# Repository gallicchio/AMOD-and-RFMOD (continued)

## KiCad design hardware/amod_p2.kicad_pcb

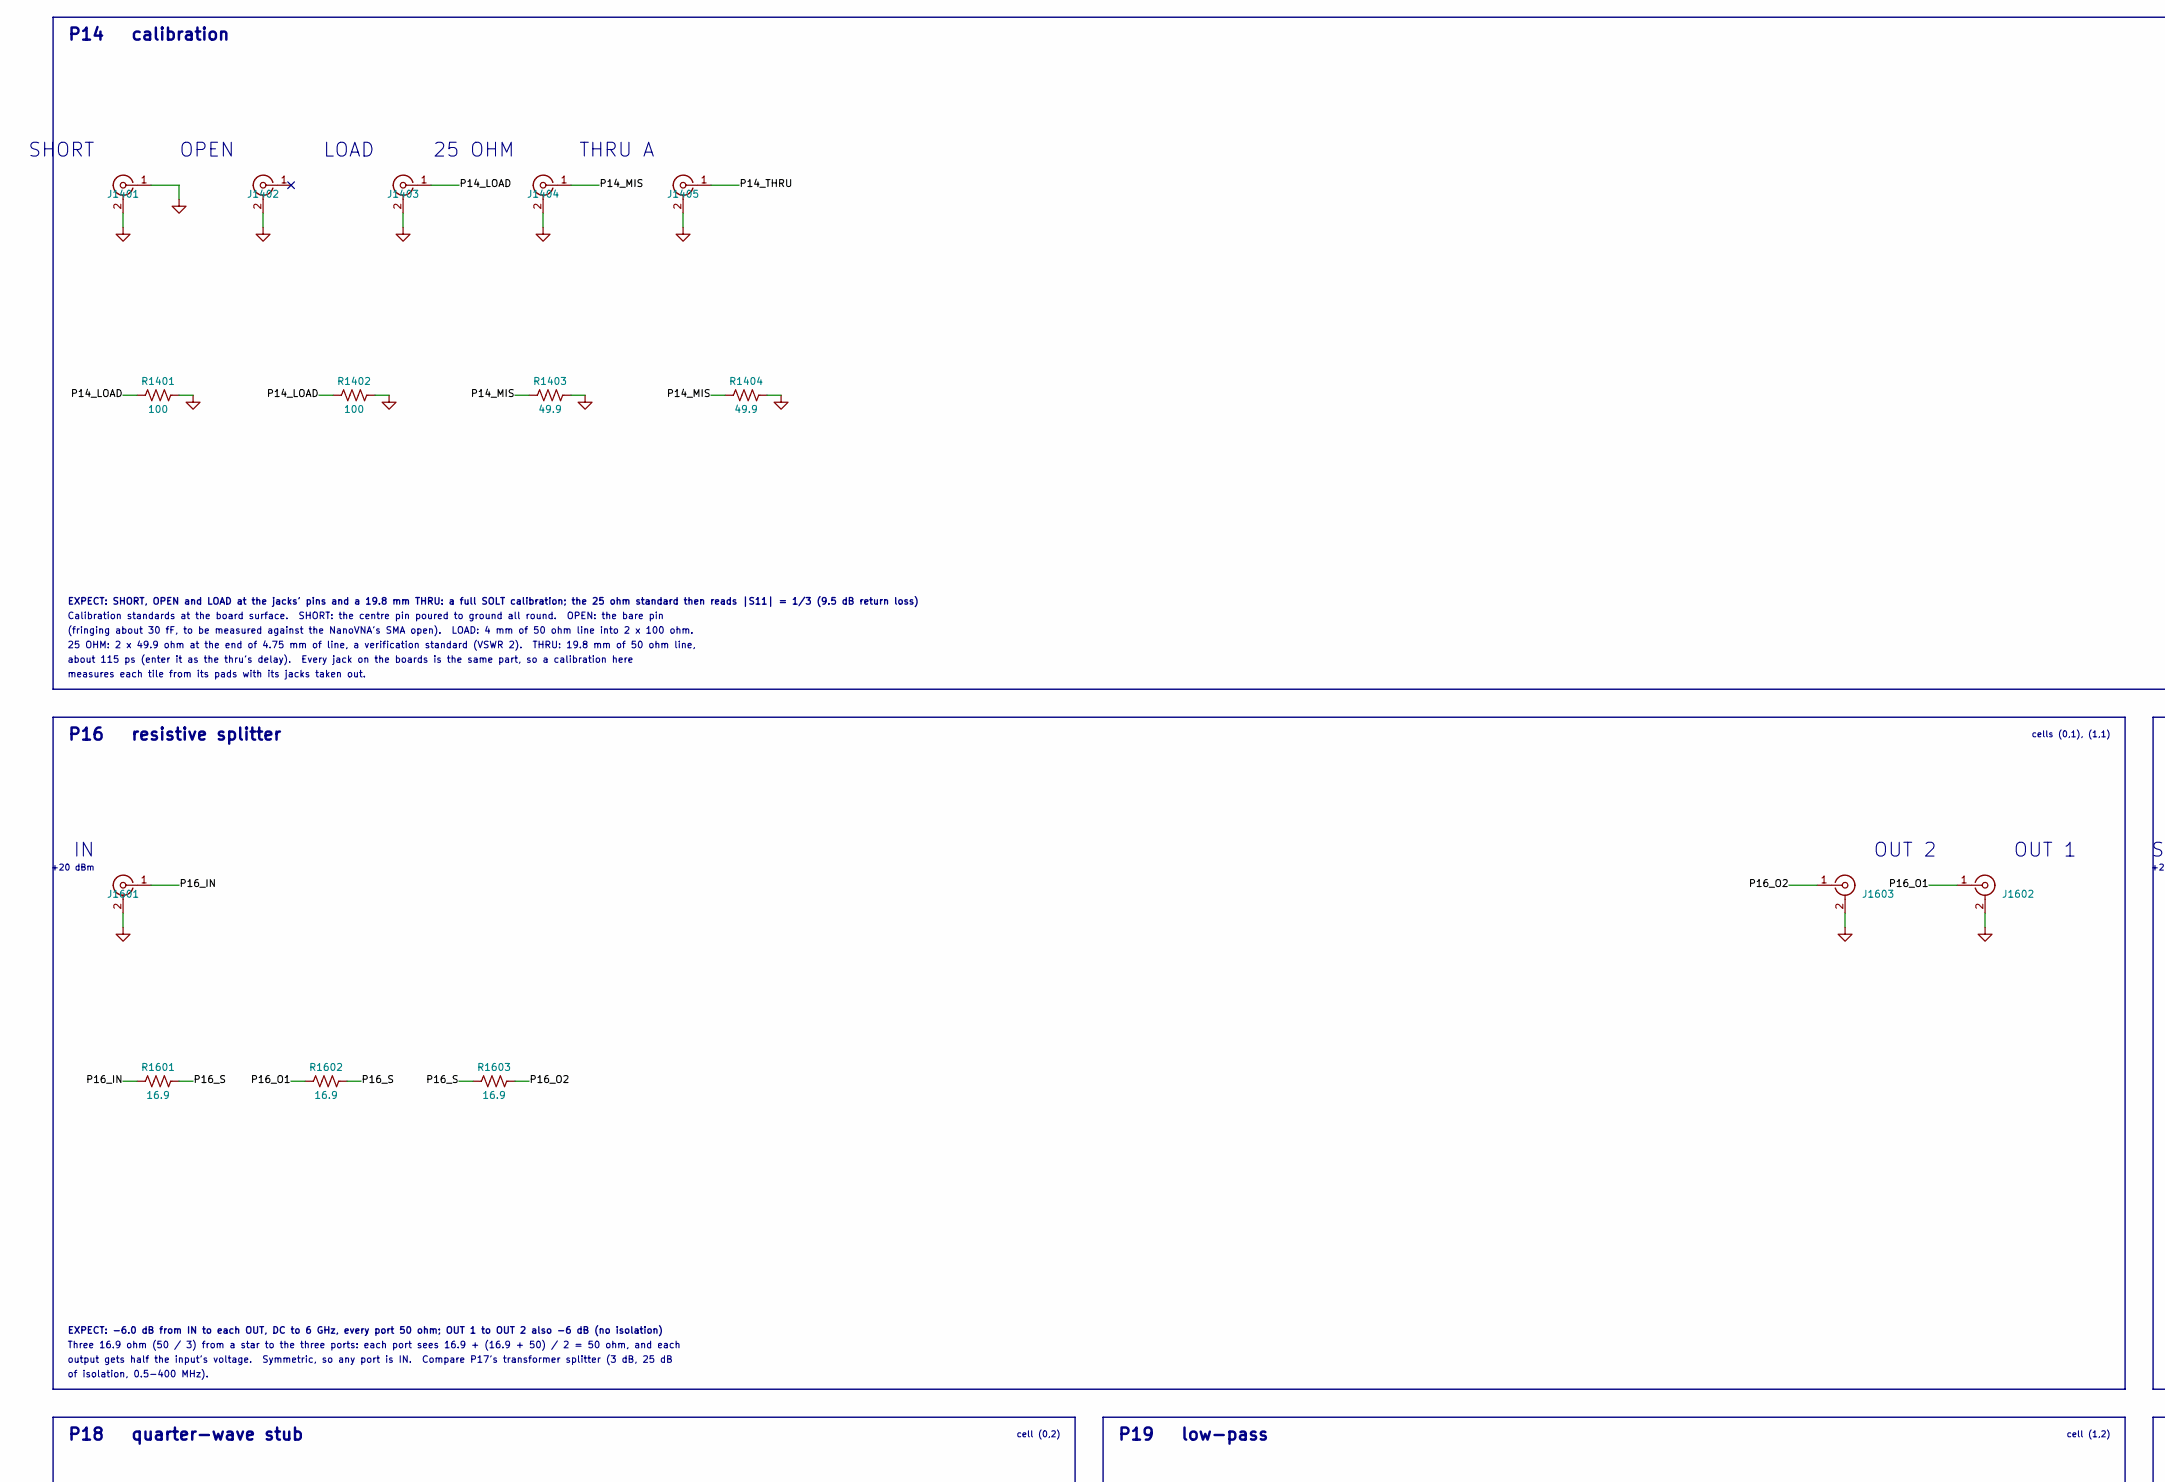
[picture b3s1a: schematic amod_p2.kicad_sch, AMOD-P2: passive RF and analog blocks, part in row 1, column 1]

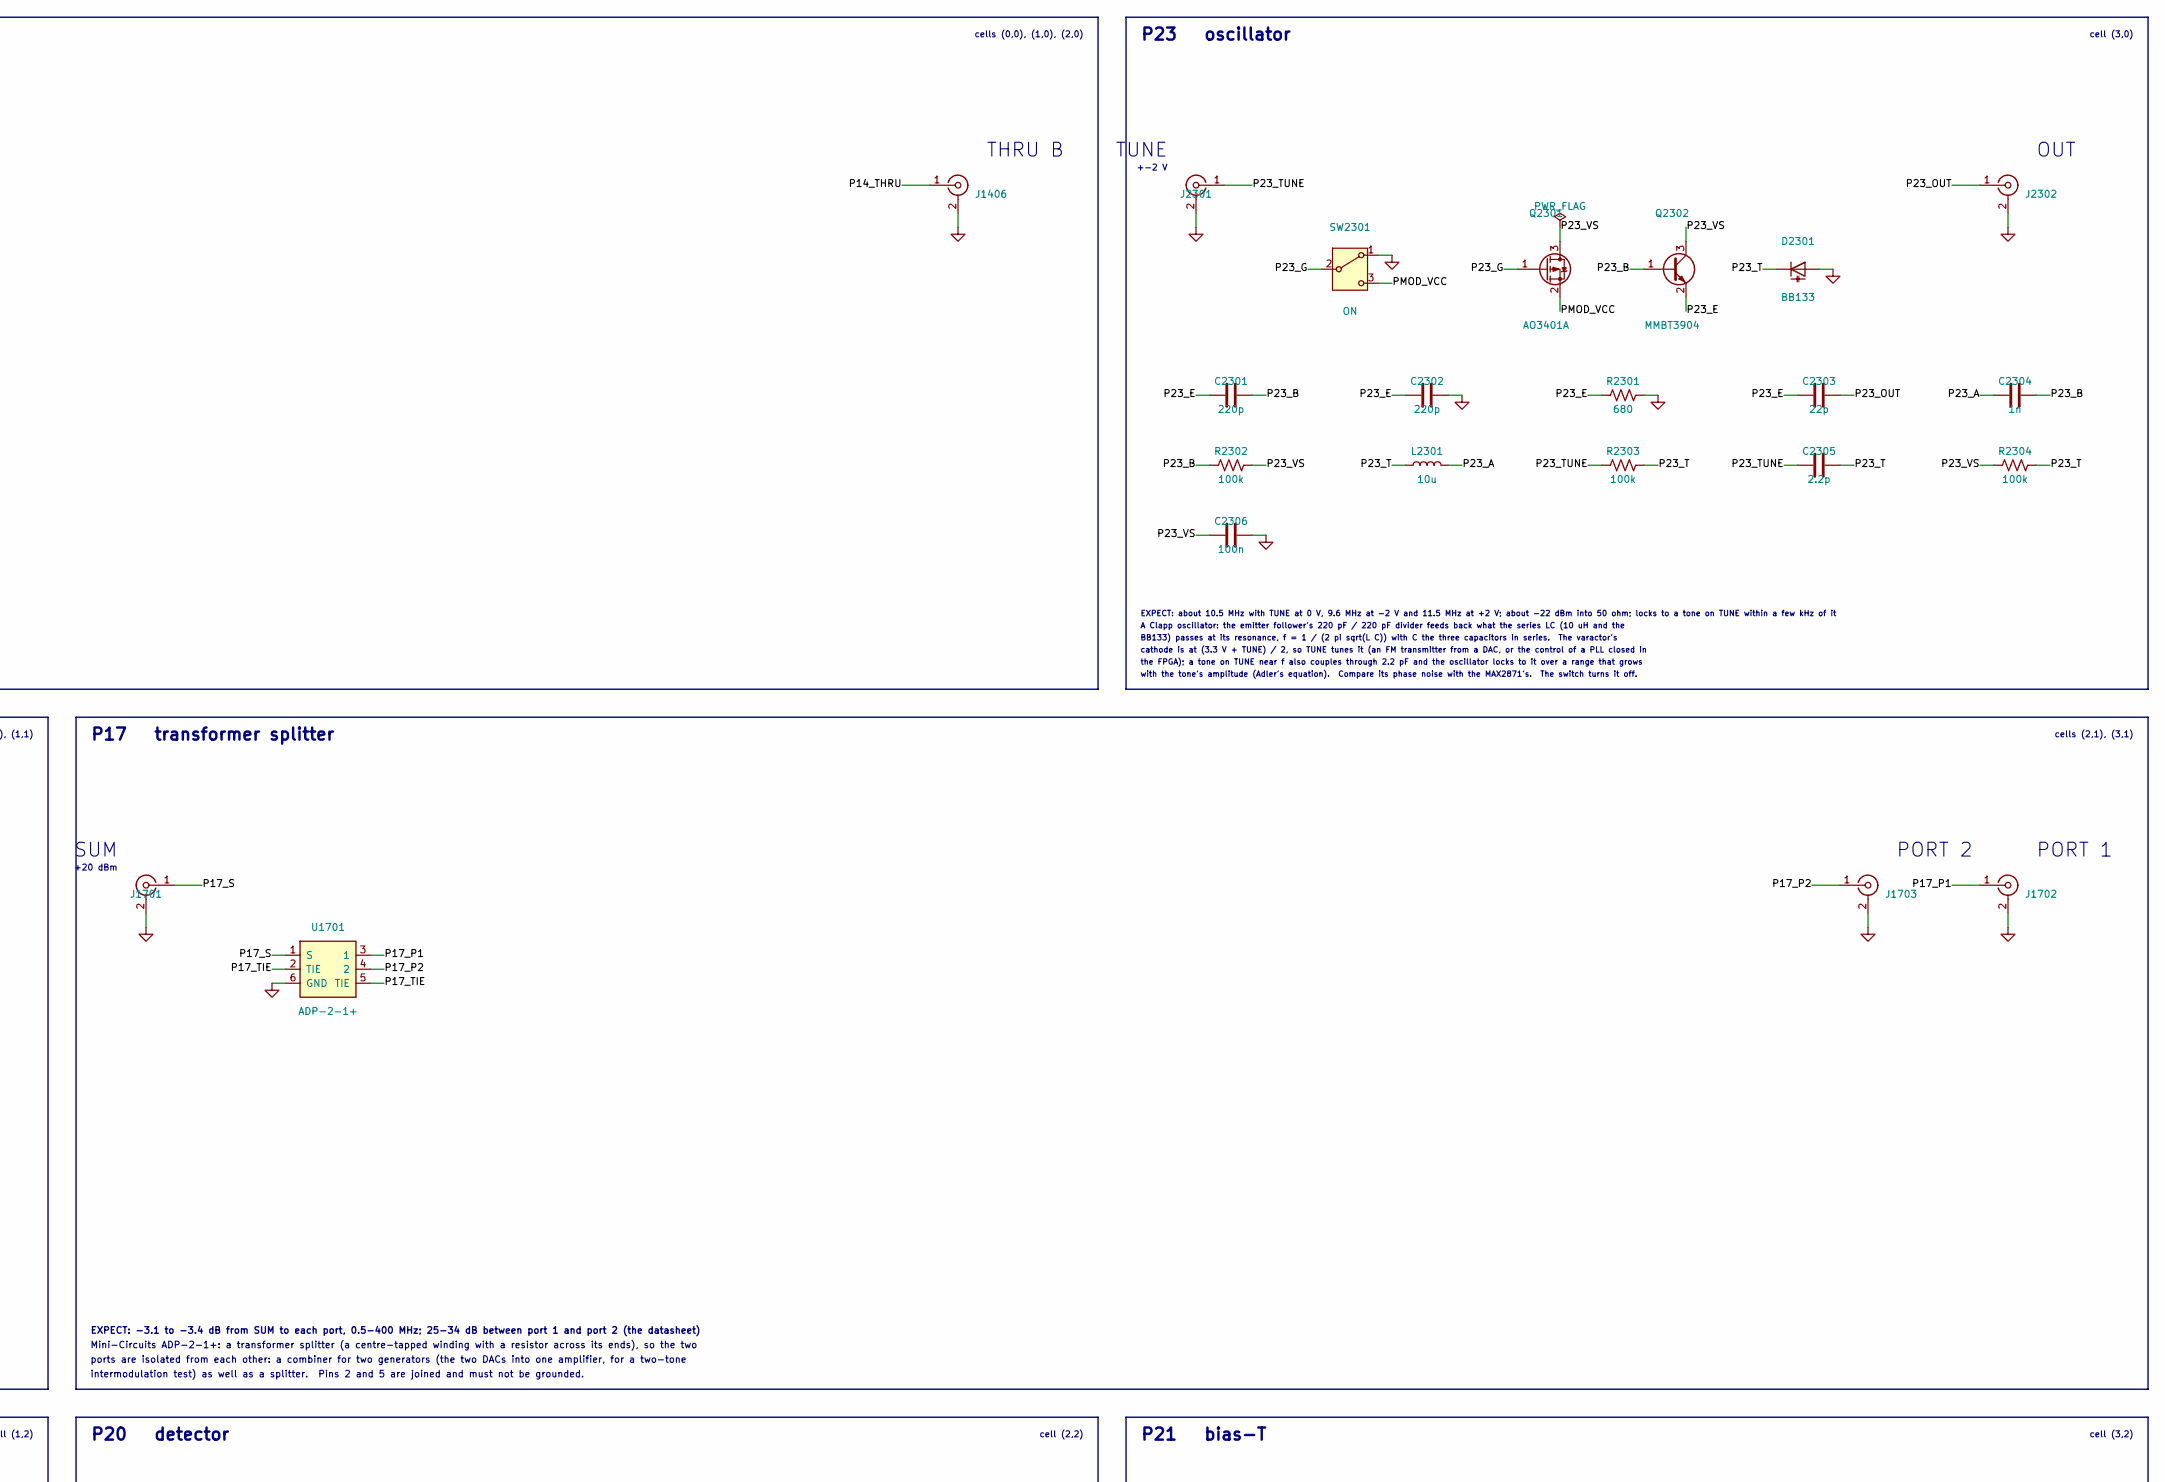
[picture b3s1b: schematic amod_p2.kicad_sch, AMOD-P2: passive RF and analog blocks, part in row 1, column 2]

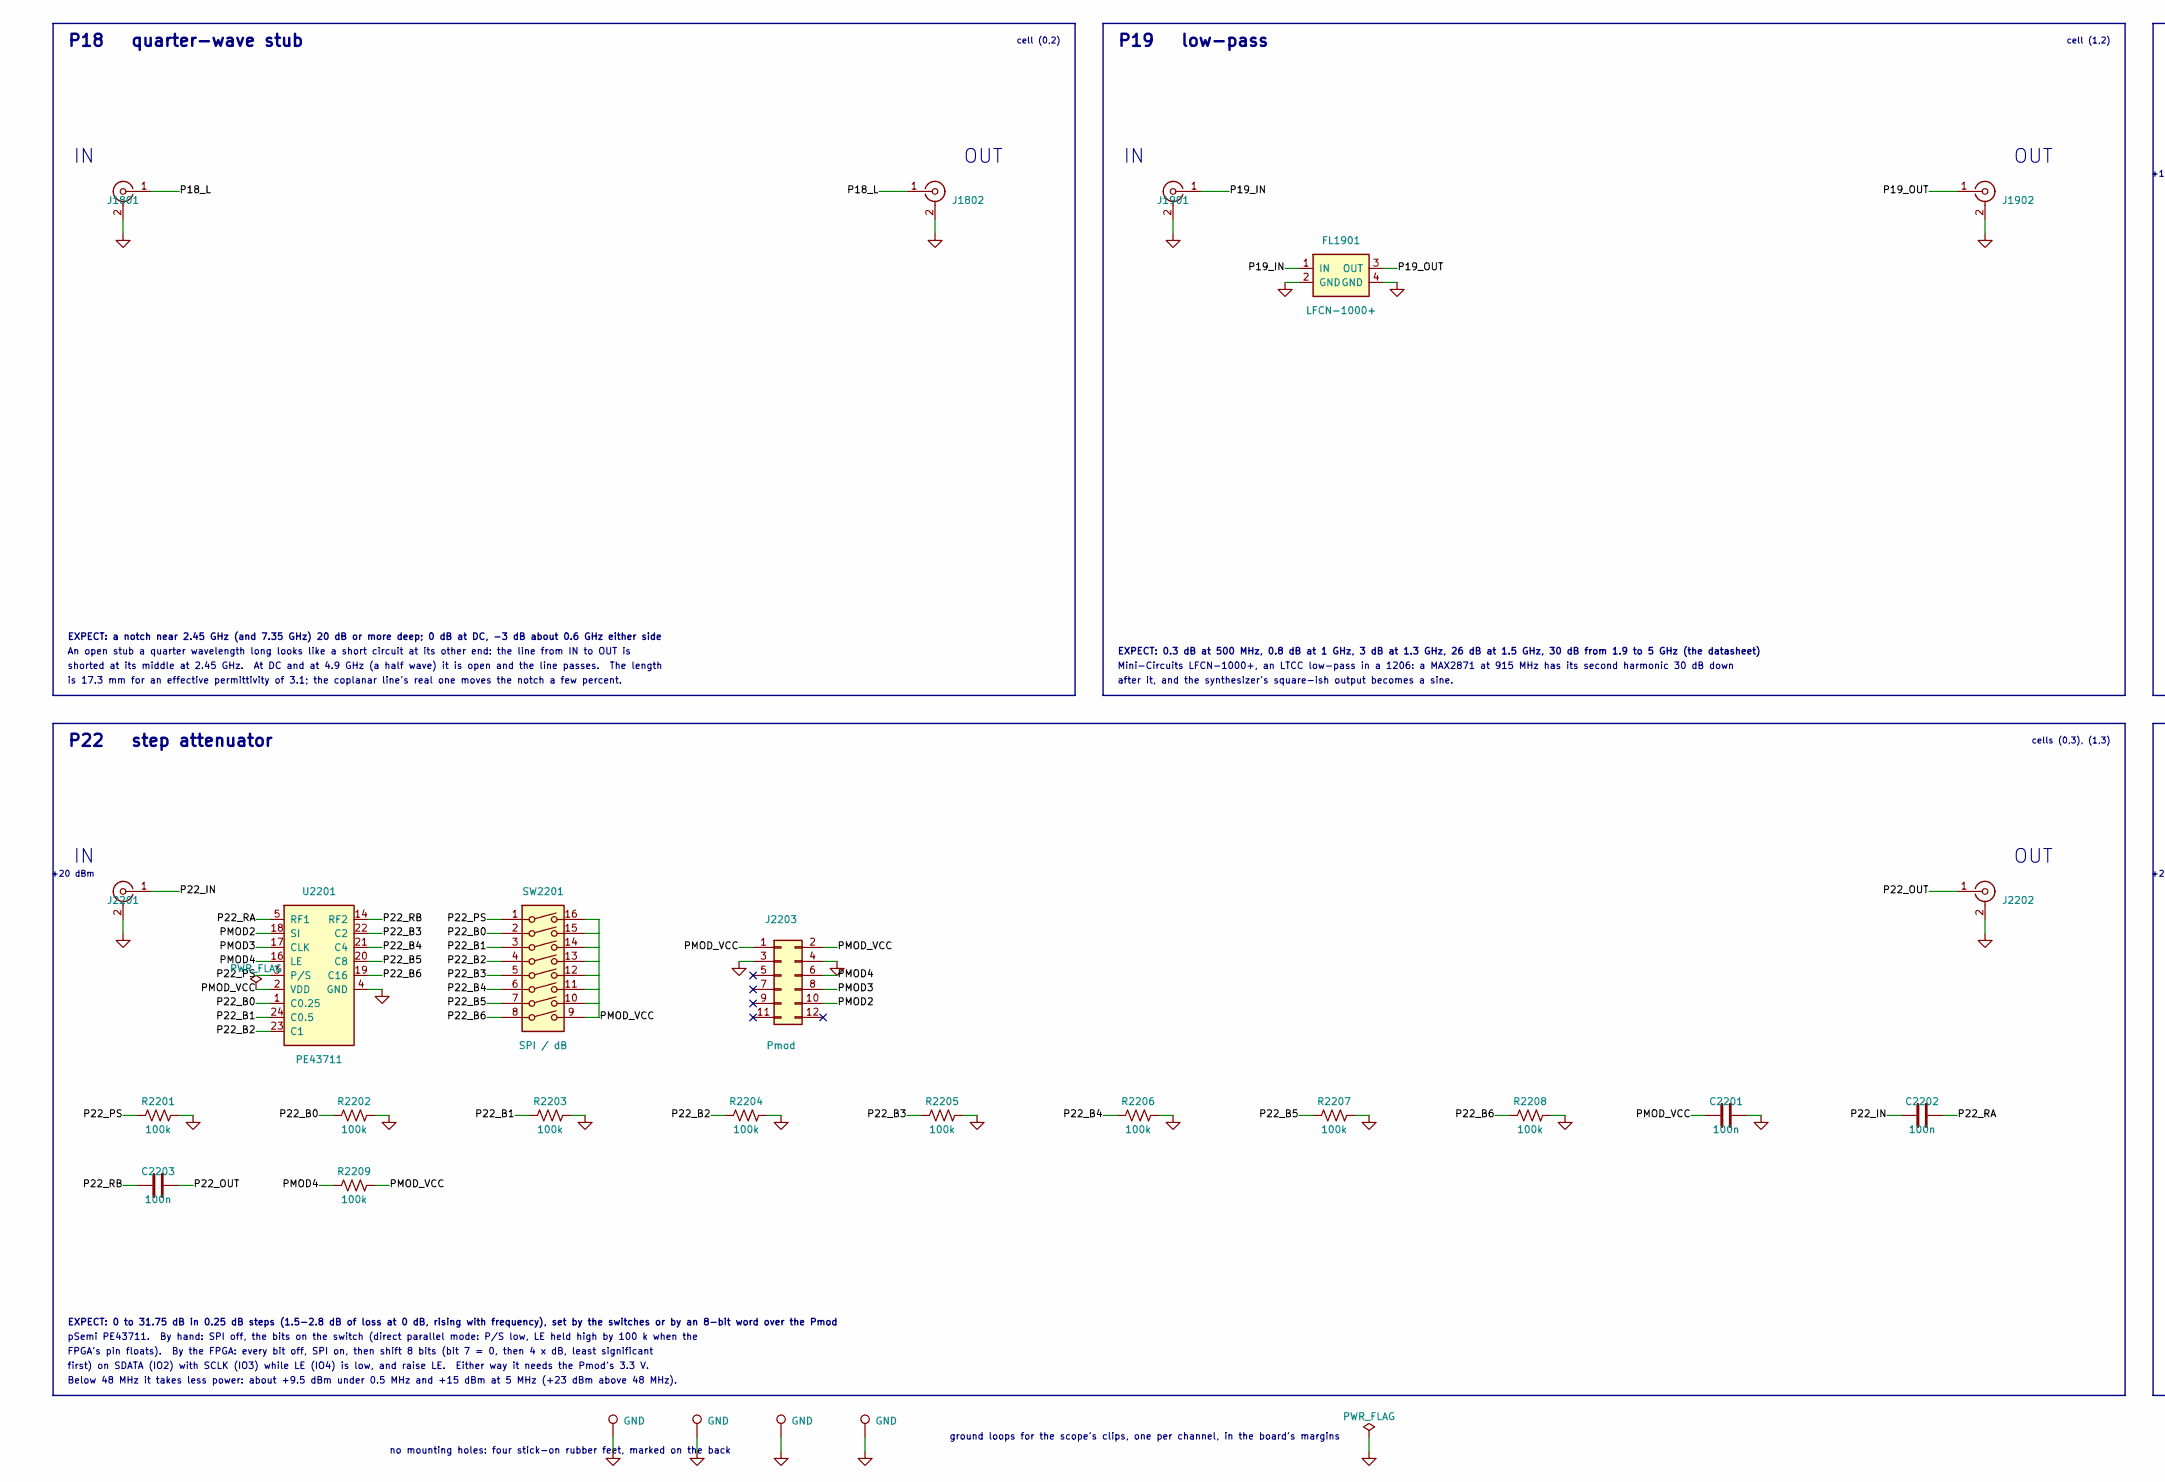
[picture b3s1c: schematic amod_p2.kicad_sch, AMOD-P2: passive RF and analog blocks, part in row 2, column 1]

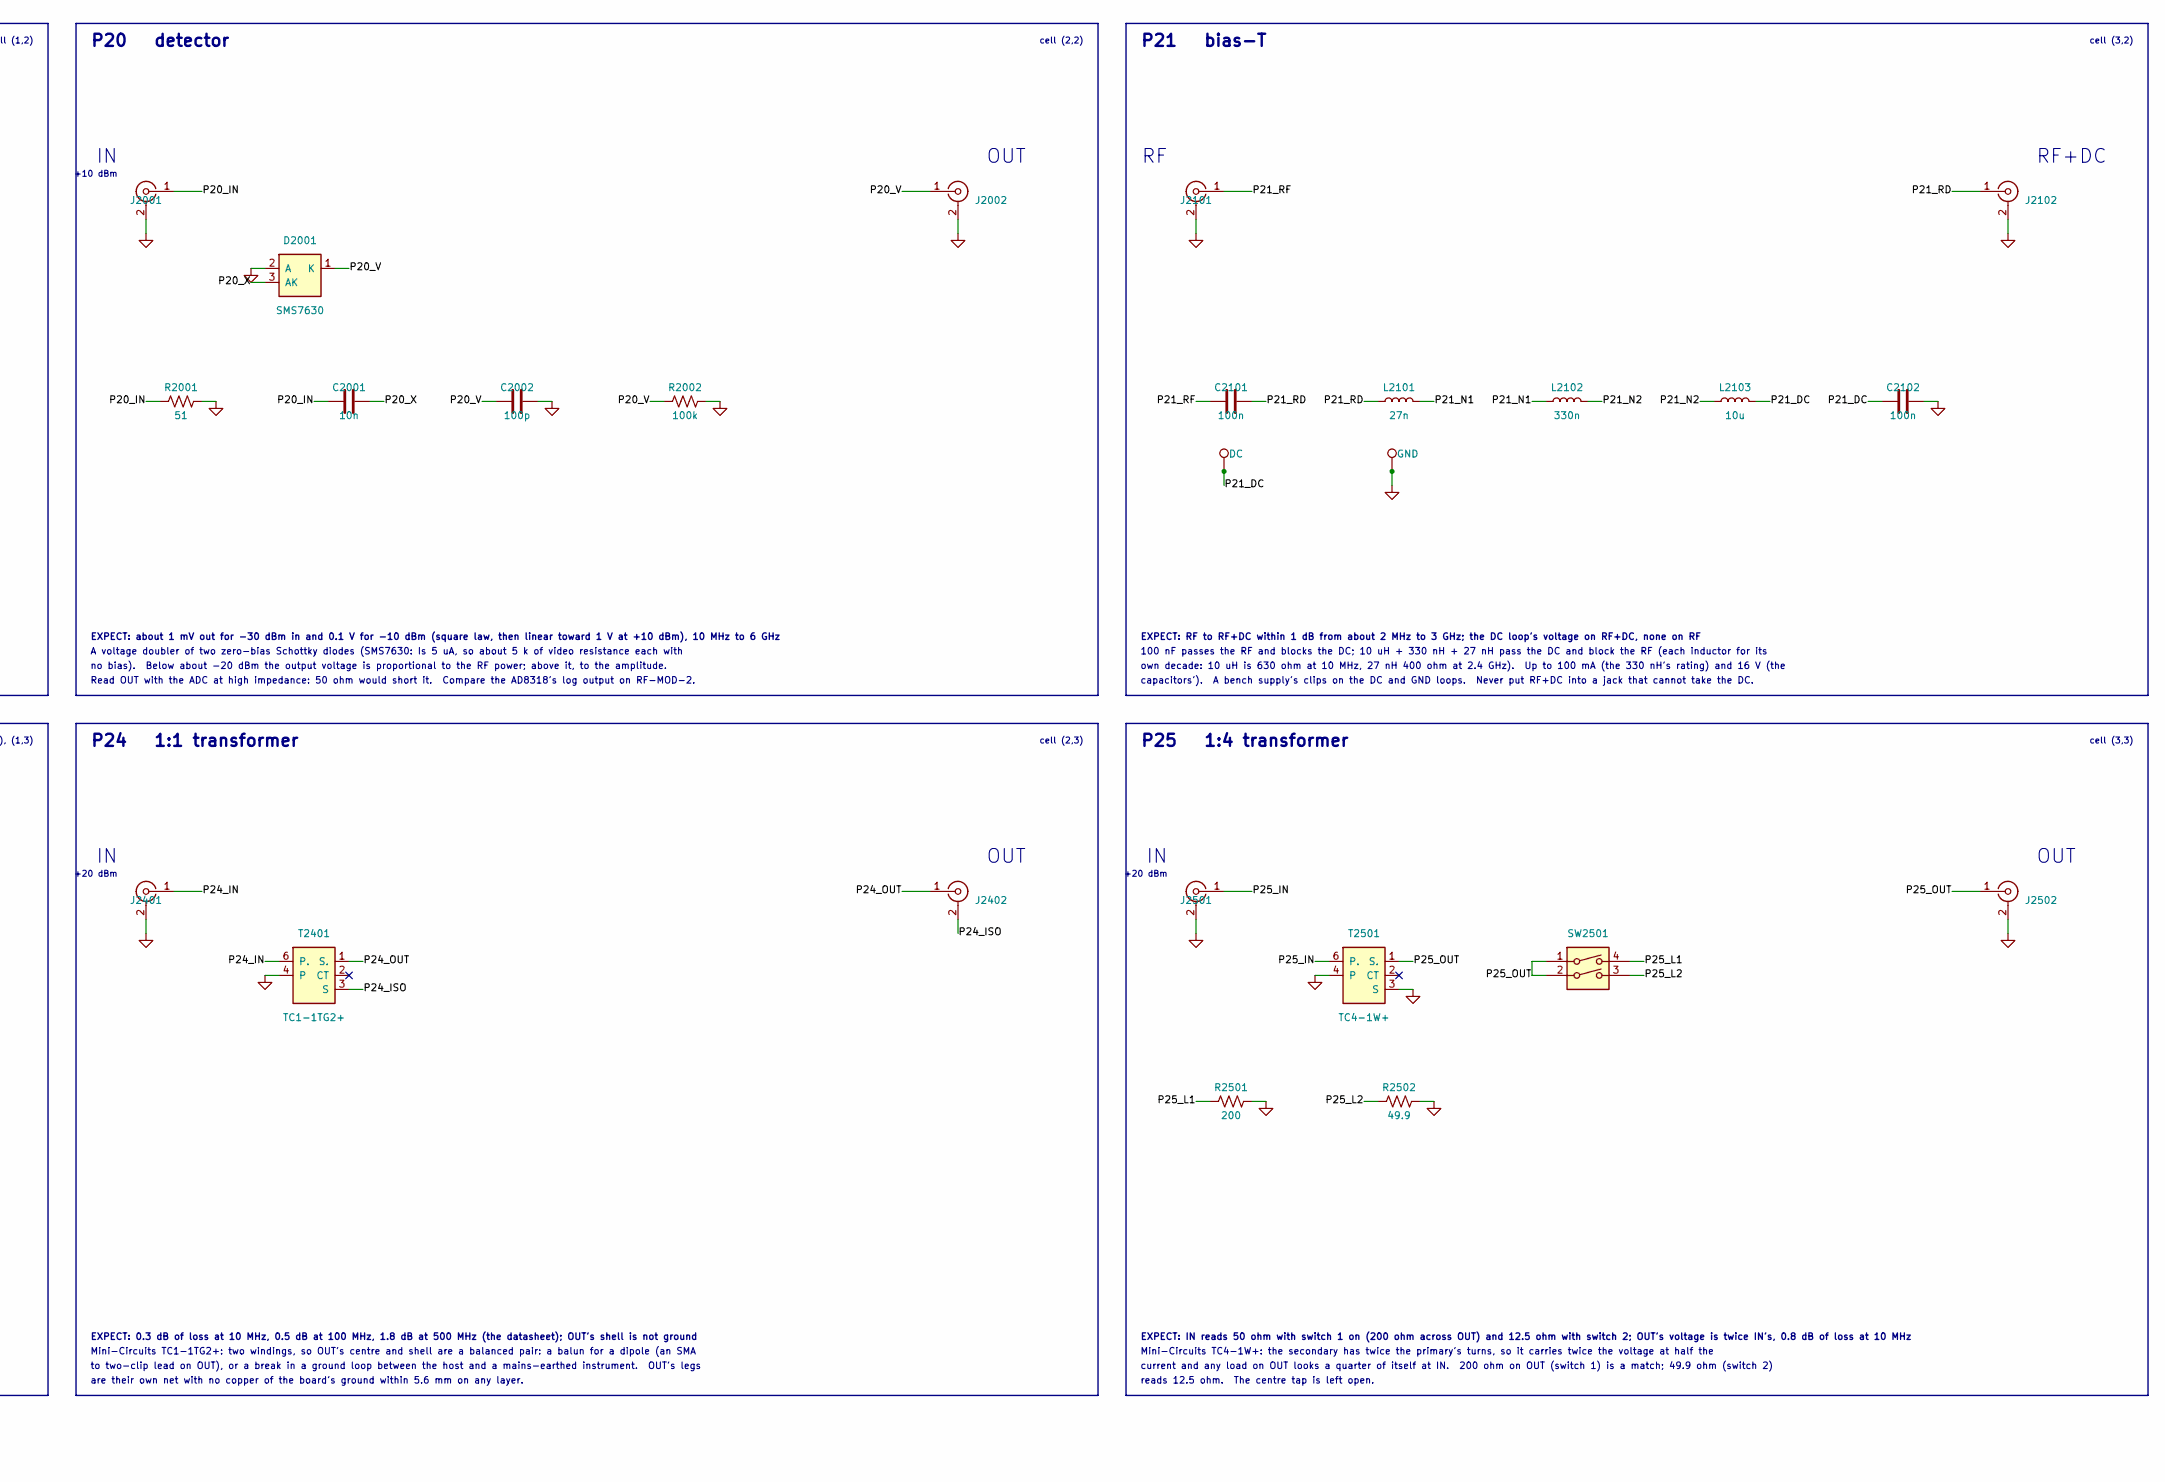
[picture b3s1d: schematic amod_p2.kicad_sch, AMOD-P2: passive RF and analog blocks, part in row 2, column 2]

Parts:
C2001: 10n; C_0402_1005Metric; MPN CL05B103KB5NNNC; LCSC C15195
C2002: 100p; C_0402_1005Metric; MPN 0402CG101J500NT; LCSC C1546
C2101, C2102, C2201, C2202, C2203, C2306: 100n; C_0402_1005Metric; MPN CL05B104KO5NNNC; LCSC C1525
C2301, C2302: 220p; C_0402_1005Metric; MPN 0402CG221J500NT; LCSC C39122
C2303: 22p; C_0402_1005Metric; MPN 0402CG220J500NT; LCSC C1555
C2304: 1n; C_0402_1005Metric; MPN 0402B102K500NT; LCSC C1523
C2305: 2.2p; C_0402_1005Metric; MPN 0402CG2R2C500NT; LCSC C1559
D2001: SMS7630; SOT-23; MPN SMS7630-006LF; LCSC C6489012
D2301: BB133; D_SOD-323; MPN BB133; LCSC C5334579
FL1901: LFCN-1000+; Filter_LTCC_1206_LFCN; MPN LFCN-1000+; LCSC C879868
J1401, J1402, J1403, J1404, J1405, J1406, J1601, J1602, J1603, J1701, J1702, J1703, J1801, J1802, J1901, J1902, J2001, J2002, J2101, J2102, J2201, J2202, J2301, J2302, J2401, J2402, J2501, J2502: SMA; SMA_BWSMA-KE-Z001_Vertical; MPN BWSMA-KE-Z001; LCSC C496549
J2203: Pmod; PinHeader_2x06_P2.54mm_Horizontal_PZ254R-12-12P; MPN PZ254R-12-12P; LCSC C492434
L2101: 27n; L_0402_1005Metric; MPN LQW15AN27NG80D; LCSC C882469
L2102: 330n; L_0603_1608Metric; MPN CS0603-R33J-S; LCSC C142165
L2103, L2301: 10u; L_1210_3225Metric; MPN NLV32T-100J-PF; LCSC C76835
Q2301: AO3401A; SOT-23; MPN AO3401A; LCSC C15127
Q2302: MMBT3904; SOT-23; MPN MMBT3904(RANGE:100-300); LCSC C20526
R1401, R1402: 100; R_0402_1005Metric; MPN 0402WGF1000TCE; LCSC C25076
R1403, R1404, R2502: 49.9; R_0402_1005Metric; MPN 0402WGF499JTCE; LCSC C25120
R1601, R1602, R1603: 16.9; R_0402_1005Metric; MPN 0402WGF169JTCE; LCSC C82287
R2001: 51; R_0402_1005Metric; MPN 0402WGF510JTCE; LCSC C25125
R2002, R2201, R2202, R2203, R2204, R2205, R2206, R2207, R2208, R2209, R2302, R2303, R2304: 100k; R_0402_1005Metric; MPN 0402WGF1003TCE; LCSC C25741
R2301: 680; R_0402_1005Metric; MPN 0402WGF6800TCE; LCSC C25130
R2501: 200; R_0402_1005Metric; MPN 0402WGF2000TCE; LCSC C25087
SW2201: SPI / dB; SW_DIP_SPSTx08_Slide_1.27mm_DSHP08; MPN DSHP08TSGET; LCSC C40738
SW2301: ON; SW_SPDT_Shouhan_MSK12C02; MPN MSK12C02; LCSC C431540
SW2501: LOAD; SW_DIP_SPSTx02_Slide_1.27mm_DSHP02; MPN DSHP02TSGET; LCSC C40735
T2401: TC1-1TG2+; MiniCircuits_AT224_5P; MPN TC1-1TG2+; LCSC C3305009
T2501: TC4-1W+; MiniCircuits_AT224_5P; MPN TC4-1W+; LCSC C879855
TP2101: DC; TestPoint_Loop_RH-5019; MPN RH-5019; LCSC C5199800
TP2102, TP9901, TP9902, TP9903, TP9904: GND; TestPoint_Loop_RH-5019; MPN RH-5019; LCSC C5199800
U1701: ADP-2-1+; MiniCircuits_CD636_ADP-2-1; MPN ADP-2-1+; LCSC C2683460
U2201: PE43711; QFN-24-1EP_4x4mm_P0.5mm_EP2.7x2.7mm; MPN PE43711B-Z; LCSC C470929

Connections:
/P14_LOAD: J1403.1 (In), R1401.1, R1402.1
/P14_MIS: J1404.1 (In), R1403.1, R1404.1
/P14_THRU: J1405.1 (In), J1406.1 (In)
/P16_IN: J1601.1 (In), R1601.1
/P16_O1: J1602.1 (In), R1602.1
/P16_O2: J1603.1 (In), R1603.2
/P16_S: R1601.2, R1602.2, R1603.1
/P17_P1: J1702.1 (In), U1701.3 (1)
/P17_P2: J1703.1 (In), U1701.4 (2)
/P17_S: J1701.1 (In), U1701.1 (S)
/P17_TIE: U1701.2 (TIE), U1701.5 (TIE)
/P18_L: J1801.1 (In), J1802.1 (In)
/P19_IN: FL1901.1 (IN), J1901.1 (In)
/P19_OUT: FL1901.3 (OUT), J1902.1 (In)
/P20_IN: C2001.1, J2001.1 (In), R2001.1
/P20_V: C2002.1, D2001.1 (K), J2002.1 (In), R2002.1
/P20_X: C2001.2, D2001.3 (AK)
/P21_DC: C2102.1, L2103.2, TP2101.1
/P21_N1: L2101.2, L2102.1
/P21_N2: L2102.2, L2103.1
/P21_RD: C2101.2, J2102.1 (In), L2101.1
/P21_RF: C2101.1, J2101.1 (In)
/P22_B0: R2202.1, SW2201.2, U2201.1 (C0.25)
/P22_B1: R2203.1, SW2201.3, U2201.24 (C0.5)
/P22_B2: R2204.1, SW2201.4, U2201.23 (C1)
/P22_B3: R2205.1, SW2201.5, U2201.22 (C2)
/P22_B4: R2206.1, SW2201.6, U2201.21 (C4)
/P22_B5: R2207.1, SW2201.7, U2201.20 (C8)
/P22_B6: R2208.1, SW2201.8, U2201.19 (C16)
/P22_IN: C2202.1, J2201.1 (In)
/P22_OUT: C2203.2, J2202.1 (In)
/P22_PS: R2201.1, SW2201.1, U2201.3 (P/S)
/P22_RA: C2202.2, U2201.5 (RF1)
/P22_RB: C2203.1, U2201.14 (RF2)
/P23_A: C2304.1, L2301.2
/P23_B: C2301.2, C2304.2, Q2302.1 (B), R2302.1
/P23_E: C2301.1, C2302.1, C2303.1, Q2302.2 (E), R2301.1
/P23_G: Q2301.1 (G), SW2301.2 (B)
/P23_OUT: C2303.2, J2302.1 (In)
/P23_T: C2305.2, D2301.1 (K), L2301.1, R2303.2, R2304.2
/P23_TUNE: C2305.1, J2301.1 (In), R2303.1
/P23_VS: C2306.1, Q2301.3 (D), Q2302.3 (C), R2302.2, R2304.1
/P24_IN: J2401.1 (In), T2401.6 (P.)
/P24_ISO: J2402.2 (Ext), T2401.3 (S)
/P24_OUT: J2402.1 (In), T2401.1 (S.)
/P25_IN: J2501.1 (In), T2501.6 (P.)
/P25_L1: R2501.1, SW2501.4
/P25_L2: R2502.1, SW2501.3
/P25_OUT: J2502.1 (In), SW2501.1, SW2501.2, T2501.1 (S.)
/PMOD2: J2203.10, U2201.18 (SI)
/PMOD3: J2203.8, U2201.17 (CLK)
/PMOD4: J2203.6, R2209.1, U2201.16 (LE)
/PMOD_VCC: C2201.1, J2203.1, J2203.2, Q2301.2 (S), R2209.2, SW2201.9, SW2201.10, SW2201.11, SW2201.12, SW2201.13, SW2201.14, SW2201.15, SW2201.16, SW2301.3 (C), U2201.2 (VDD)
GND: C2002.2, C2102.2, C2201.2, C2302.2, C2306.2, D2001.2 (A), D2301.2 (A), FL1901.2 (GND), FL1901.4 (GND), J1401.1 (In), J1401.2 (Ext), J1402.2 (Ext), J1403.2 (Ext), J1404.2 (Ext), J1405.2 (Ext), J1406.2 (Ext), J1601.2 (Ext), J1602.2 (Ext), J1603.2 (Ext), J1701.2 (Ext), J1702.2 (Ext), J1703.2 (Ext), J1801.2 (Ext), J1802.2 (Ext), J1901.2 (Ext), J1902.2 (Ext), J2001.2 (Ext), J2002.2 (Ext), J2101.2 (Ext), J2102.2 (Ext), J2201.2 (Ext), J2202.2 (Ext), J2203.3, J2203.4, J2301.2 (Ext), J2302.2 (Ext), J2401.2 (Ext), J2501.2 (Ext), J2502.2 (Ext), R1401.2, R1402.2, R1403.2, R1404.2, R2001.2, R2002.2, R2201.2, R2202.2, R2203.2, R2204.2, R2205.2, R2206.2, R2207.2, R2208.2, R2301.2, R2501.2, R2502.2, SW2301.1 (A), T2401.4, T2501.3 (S), T2501.4, TP2102.1, TP9901.1, TP9902.1, TP9903.1, TP9904.1, U1701.6 (GND), U2201.4 (GND), U2201.6 (GND), U2201.7 (GND), U2201.8 (GND), U2201.9 (GND), U2201.10 (GND), U2201.11 (GND), U2201.12 (GND), U2201.13 (GND), U2201.15 (GND), U2201.25 (GND)

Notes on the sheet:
SUM
cells (2,1), (3,1)
EXPECT: -3.1 to -3.4 dB from SUM to each port, 0.5-400 MHz; 25-34 dB between port 1 and port 2 (the datasheet)
OUT
P18 quarter-wave stub
EXPECT: 0.3 dB of loss at 10 MHz, 0.5 dB at 100 MHz, 1.8 dB at 500 MHz (the datasheet); OUT's shell is not ground
EXPECT: 0 to 31.75 dB in 0.25 dB steps (1.5-2.8 dB of loss at 0 dB, rising with frequency), set by the switches or by an 8-bit word over the Pmod
cells (0,0), (1,0), (2,0)
cell (0,2)
measures each tile from its pads with its jacks taken out.
RF+DC
25 OHM: 2 x 49.9 ohm at the end of 4.75 mm of line, a verification standard (VSWR 2). THRU: 19.8 mm of 50 ohm line,
P25 1:4 transformer
P17 transformer splitter
cell (3,3)
An open stub a quarter wavelength long looks like a short circuit at its other end: the line from IN to OUT is
(fringing about 30 fF, to be measured against the NanoVNA's SMA open). LOAD: 4 mm of 50 ohm line into 2 x 100 ohm.
25 OHM
PORT 2
A voltage doubler of two zero-bias Schottky diodes (SMS7630: Is 5 uA, so about 5 k of video resistance each with
OUT 2
THRU A
+20 dBm
EXPECT: SHORT, OPEN and LOAD at the jacks' pins and a 19.8 mm THRU: a full SOLT calibration; the 25 ohm standard then reads |S11| = 1/3 (9.5 dB return loss)
LOAD
the FPGA); a tone on TUNE near f also couples through 2.2 pF and the oscillator locks to it over a range that grows
EXPECT: RF to RF+DC within 1 dB from about 2 MHz to 3 GHz; the DC loop's voltage on RF+DC, none on RF
are their own net with no copper of the board's ground within 5.6 mm on any layer.
of isolation, 0.5-400 MHz).
current and any load on OUT looks a quarter of itself at IN. 200 ohm on OUT (switch 1) is a match; 49.9 ohm (switch 2)
EXPECT: a notch near 2.45 GHz (and 7.35 GHz) 20 dB or more deep; 0 dB at DC, -3 dB about 0.6 GHz either side
EXPECT: -6.0 dB from IN to each OUT, DC to 6 GHz, every port 50 ohm; OUT 1 to OUT 2 also -6 dB (no isolation)
no bias). Below about -20 dBm the output voltage is proportional to the RF power; above it, to the amplitude.
cell (2,3)
capacitors'). A bench supply's clips on the DC and GND loops. Never put RF+DC into a jack that cannot take the DC.
EXPECT: about 1 mV out for -30 dBm in and 0.1 V for -10 dBm (square law, then linear toward 1 V at +10 dBm), 10 MHz to 6 GHz
Mini-Circuits ADP-2-1+: a transformer splitter (a centre-tapped winding with a resistor across its ends), so the two
OUT 1
cells (0,3), (1,3)
ground loops for the scope's clips, one per channel, in the board's margins

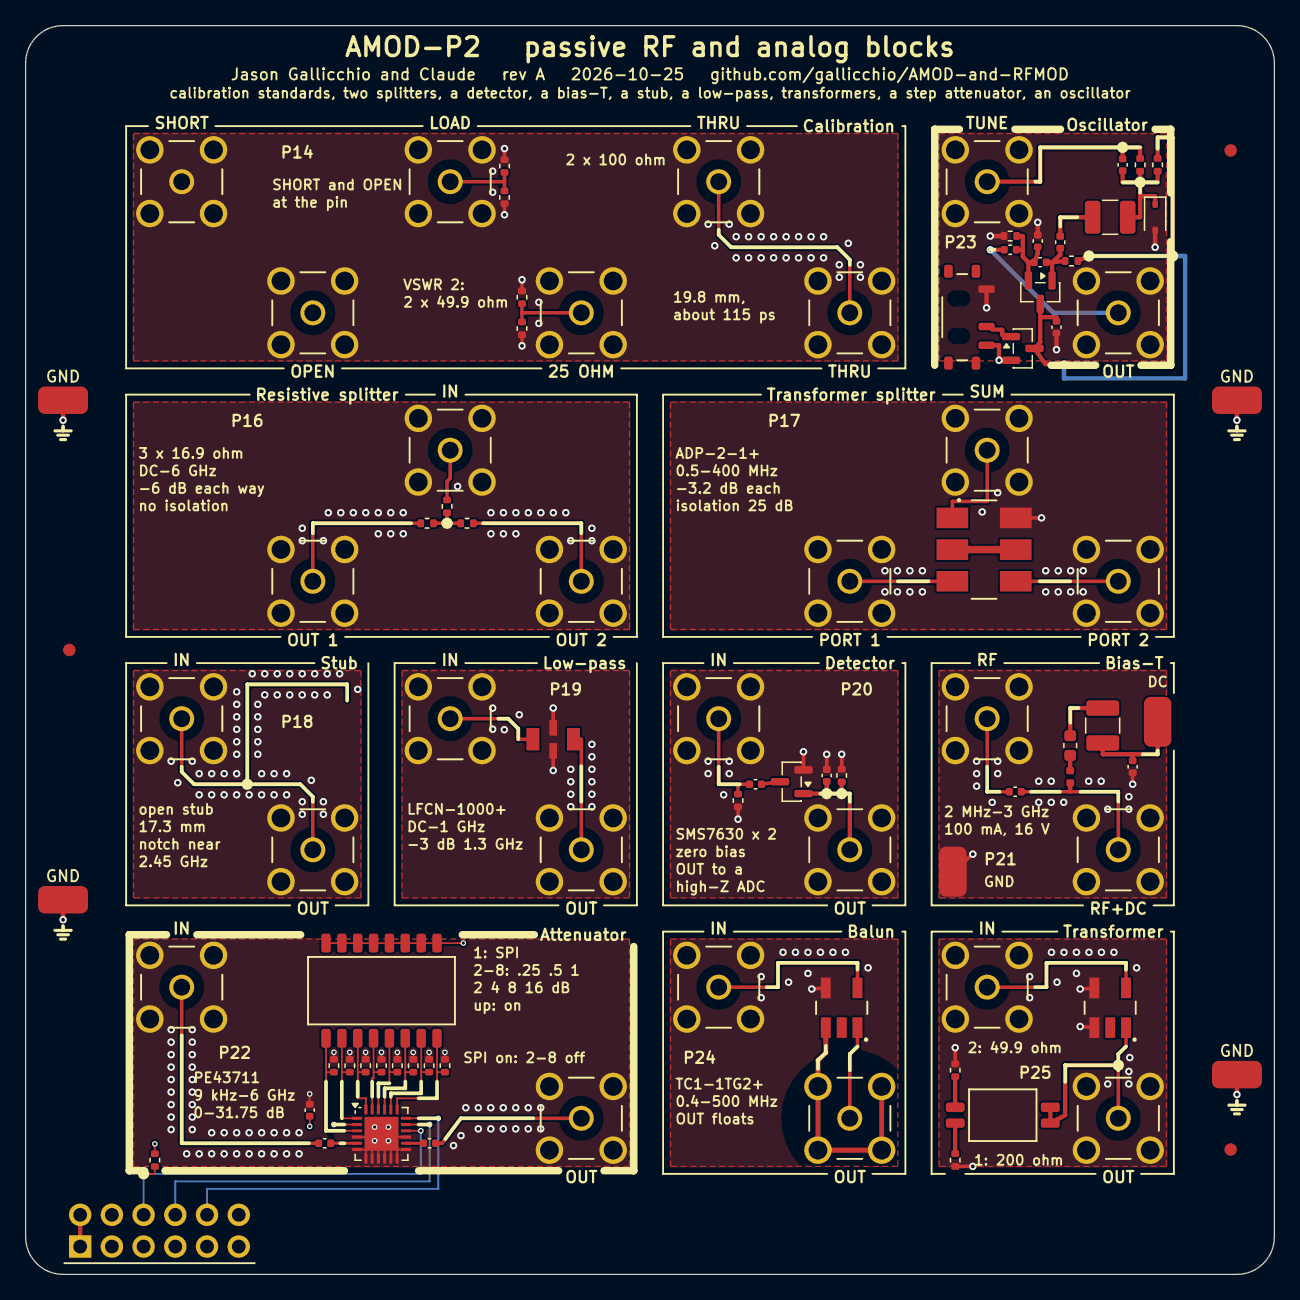
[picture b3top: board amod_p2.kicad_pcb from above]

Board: 4 copper layers, 100.0 x 100.0 mm, 88 parts (0 on the bottom side), 54 nets.
